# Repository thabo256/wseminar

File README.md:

# W-Seminar

v0.1.0

## Inspiration

[key-ripper by Brian Schwind](https://github.com/bschwind/key-ripper)

## License

This project is licensed under the GNU General Public License (GPL). See the [`LICENSE`](/LICENSE) file in the root for details.

However, the code in the `firmware/` directory is licensed under the MIT License. See the [`LICENSE`](/firmware/LICENSE) file in that directory for details.

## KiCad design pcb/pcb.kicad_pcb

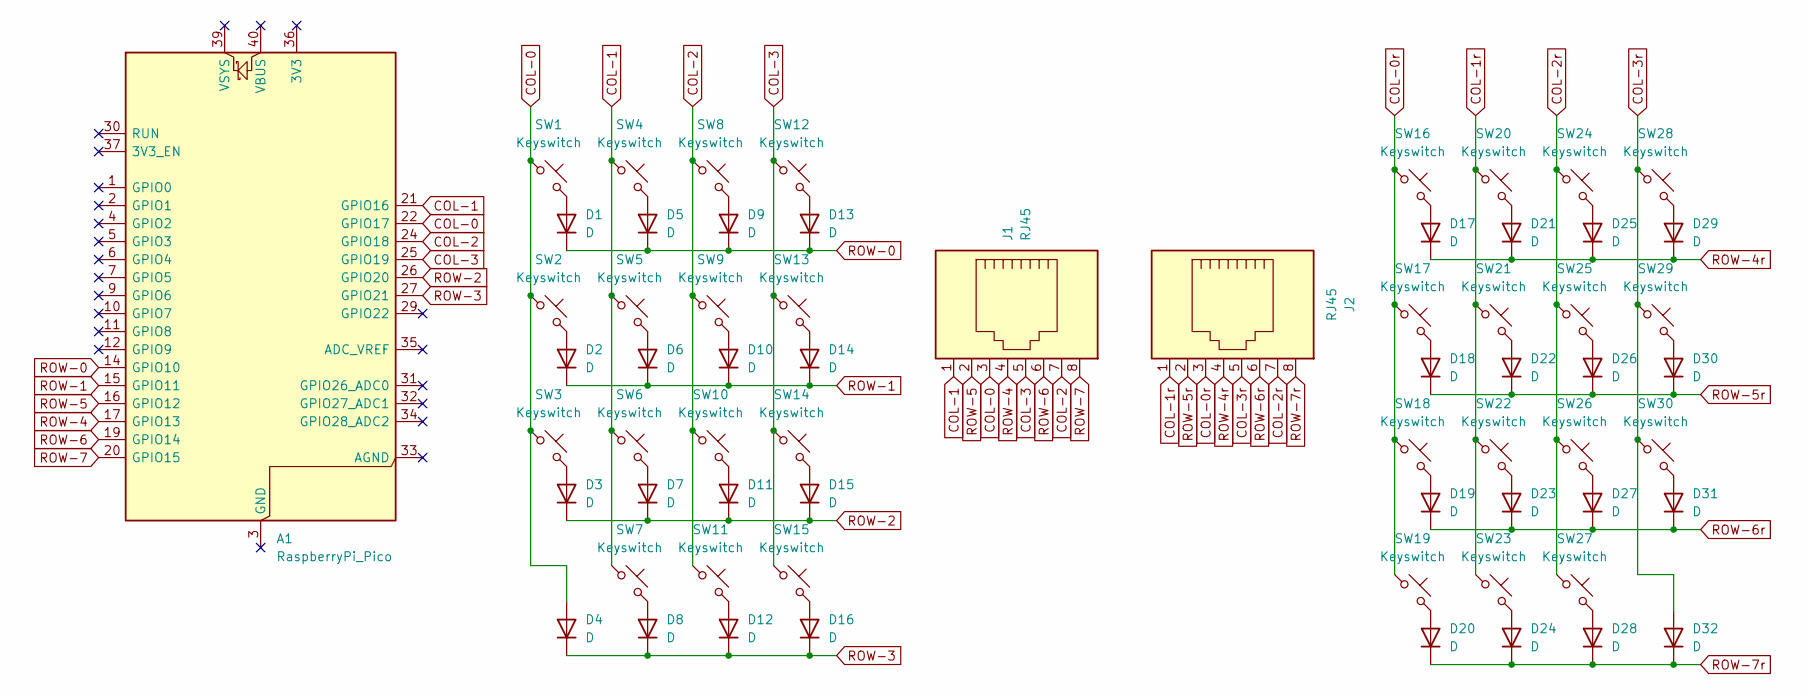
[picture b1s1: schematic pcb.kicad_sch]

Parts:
A1: RaspberryPi_Pico; RaspberryPi_Pico_Common_Unspecified
D1, D2, D3, D4, D5, D6, D7, D8, D9, D10, D11, D12, D13, D14, D15, D16, D17, D18, D19, D20, D21, D22, D23, D24, D25, D26, D27, D28, D29, D30, D31, D32: D; D_DO-35_SOD27_P7.62mm_Horizontal
J1, J2: RJ45; RJ45_Amphenol_54602-x08_Horizontal
SW1, SW2, SW3, SW4, SW5, SW6, SW7, SW8, SW9, SW10, SW11, SW12, SW13, SW14, SW15, SW16, SW17, SW18, SW19, SW20, SW21, SW22, SW23, SW24, SW25, SW26, SW27, SW28, SW29, SW30: Keyswitch; SW_Gateron_LowProfile_HotSwap_THT

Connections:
COL-0: A1.22 (GPIO17), D4.2 (A), J1.3, SW1.1, SW2.1, SW3.1
COL-0r: J2.3, SW16.1, SW17.1, SW18.1, SW19.1
COL-1: A1.21 (GPIO16), J1.1, SW4.1, SW5.1, SW6.1, SW7.1
COL-1r: J2.1, SW20.1, SW21.1, SW22.1, SW23.1
COL-2: A1.24 (GPIO18), J1.7, SW8.1, SW9.1, SW10.1, SW11.1
COL-2r: J2.7, SW24.1, SW25.1, SW26.1, SW27.1
COL-3: A1.25 (GPIO19), J1.5, SW12.1, SW13.1, SW14.1, SW15.1
COL-3r: D32.2 (A), J2.5, SW28.1, SW29.1, SW30.1
unnamed: D1.2 (A), SW1.2
unnamed: D2.2 (A), SW2.2
unnamed: D3.2 (A), SW3.2
unnamed: D5.2 (A), SW4.2
unnamed: D6.2 (A), SW5.2
unnamed: D7.2 (A), SW6.2
unnamed: D8.2 (A), SW7.2
unnamed: D9.2 (A), SW8.2
unnamed: D10.2 (A), SW9.2
unnamed: D11.2 (A), SW10.2
unnamed: D12.2 (A), SW11.2
unnamed: D13.2 (A), SW12.2
unnamed: D14.2 (A), SW13.2
unnamed: D15.2 (A), SW14.2
unnamed: D16.2 (A), SW15.2
unnamed: D17.2 (A), SW16.2
unnamed: D18.2 (A), SW17.2
unnamed: D19.2 (A), SW18.2
unnamed: D20.2 (A), SW19.2
unnamed: D21.2 (A), SW20.2
unnamed: D22.2 (A), SW21.2
unnamed: D23.2 (A), SW22.2
unnamed: D24.2 (A), SW23.2
unnamed: D25.2 (A), SW24.2
unnamed: D26.2 (A), SW25.2
unnamed: D27.2 (A), SW26.2
unnamed: D28.2 (A), SW27.2
unnamed: D29.2 (A), SW28.2
unnamed: D30.2 (A), SW29.2
unnamed: D31.2 (A), SW30.2
ROW-0: A1.14 (GPIO10), D1.1 (K), D5.1 (K), D9.1 (K), D13.1 (K)
ROW-1: A1.15 (GPIO11), D2.1 (K), D6.1 (K), D10.1 (K), D14.1 (K)
ROW-2: A1.26 (GPIO20), D3.1 (K), D7.1 (K), D11.1 (K), D15.1 (K)
ROW-3: A1.27 (GPIO21), D4.1 (K), D8.1 (K), D12.1 (K), D16.1 (K)
ROW-4: A1.17 (GPIO13), J1.4
ROW-4r: D17.1 (K), D21.1 (K), D25.1 (K), D29.1 (K), J2.4
ROW-5: A1.16 (GPIO12), J1.2
ROW-5r: D18.1 (K), D22.1 (K), D26.1 (K), D30.1 (K), J2.2
ROW-6: A1.19 (GPIO14), J1.6
ROW-6r: D19.1 (K), D23.1 (K), D27.1 (K), D31.1 (K), J2.6
ROW-7: A1.20 (GPIO15), J1.8
ROW-7r: D20.1 (K), D24.1 (K), D28.1 (K), D32.1 (K), J2.8

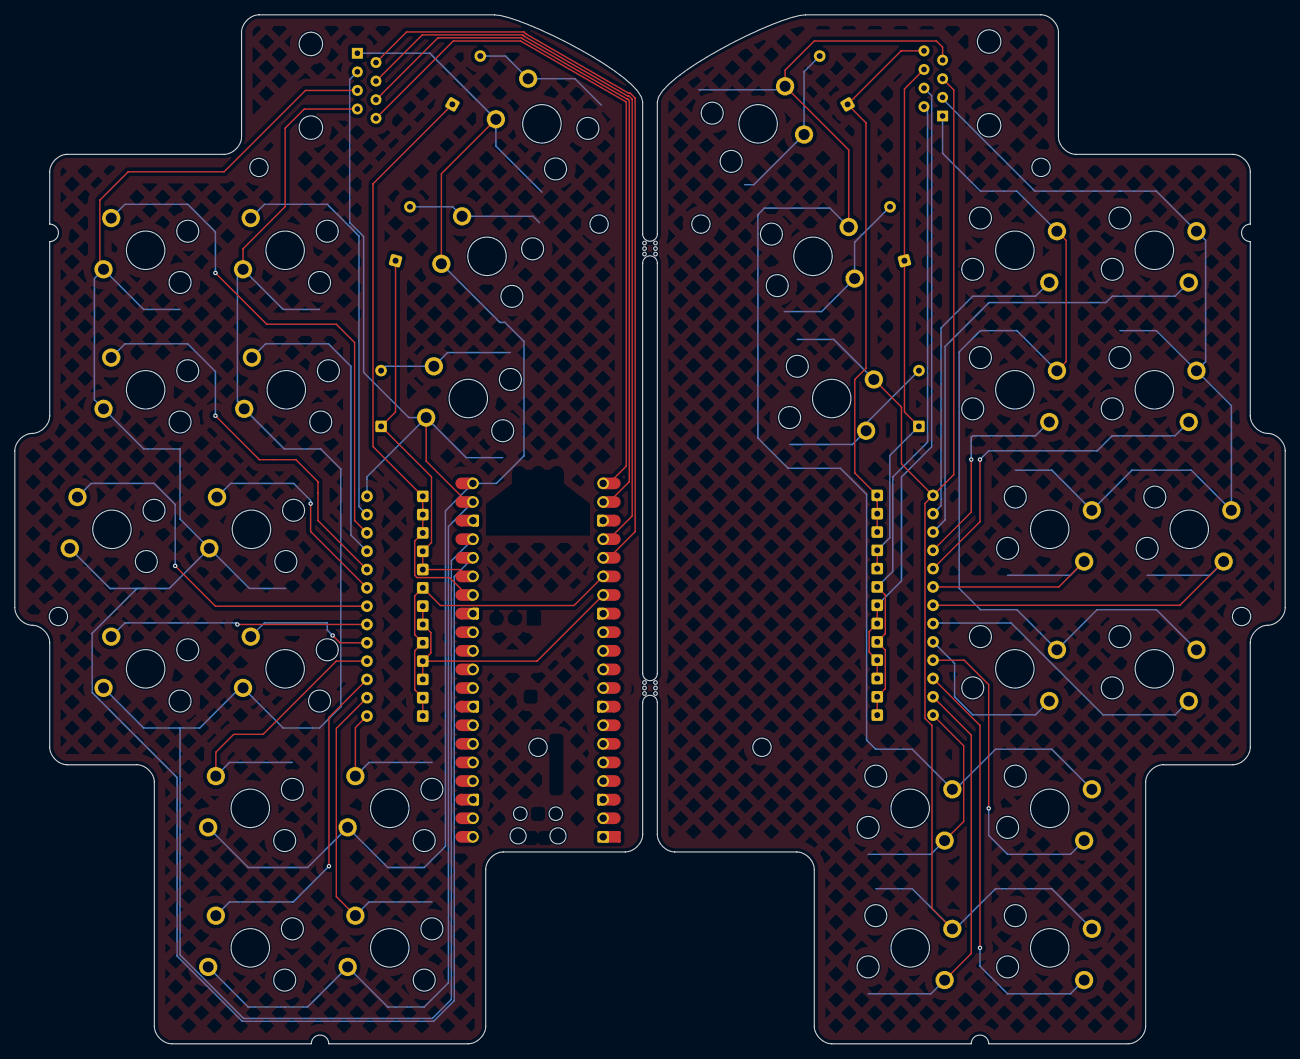
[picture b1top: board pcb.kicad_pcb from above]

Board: 2 copper layers, 173.5 x 140.5 mm, 67 parts (0 on the bottom side), 50 nets.

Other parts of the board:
mouse-bite-2mm-slot, mouse-bite-2mm-slot#2: VAL**; mouse-bite-2mm-slot

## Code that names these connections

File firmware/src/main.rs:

#![no_std]
#![no_main]

use bsp::entry;
use bsp::hal;
use core::{convert::Infallible, panic};
use cortex_m::prelude::*;
use defmt::*;
use defmt_rtt as _;
use embedded_hal::digital::{InputPin, OutputPin, PinState};
use fugit::ExtU32;
use panic_probe as _;
use usb_device::class_prelude::*;
use usb_device::prelude::*;
use usbd_human_interface_device::page::Keyboard;
use usbd_human_interface_device::prelude::*;

// Provide an alias for our BSP so we can switch targets quickly.
use rp_pico as bsp;

use bsp::hal::{
    clocks::{init_clocks_and_plls, Clock},
    pac,
    sio::Sio,
    watchdog::Watchdog,
};

const NUM_COLS: usize = 4;
const NUM_ROWS: usize = 4;

#[entry]
fn main() -> ! {
    info!("Program start");
    let mut pac = pac::Peripherals::take().unwrap();
    let core = pac::CorePeripherals::take().unwrap();
    let mut watchdog = Watchdog::new(pac.WATCHDOG);
    let sio = Sio::new(pac.SIO);

    // External high-speed crystal on the pico board is 12Mhz
    let external_xtal_freq_hz = 12_000_000u32;
    let clocks = init_clocks_and_plls(
        external_xtal_freq_hz,
        pac.XOSC,
        pac.CLOCKS,
        pac.PLL_SYS,
        pac.PLL_USB,
        &mut pac.RESETS,
        &mut watchdog,
    )
    .ok()
    .unwrap();

    let timer = hal::Timer::new(pac.TIMER, &mut pac.RESETS, &clocks);

    let mut delay = cortex_m::delay::Delay::new(core.SYST, clocks.system_clock.freq().to_Hz());

    let pins = bsp::Pins::new(
        pac.IO_BANK0,
        pac.PADS_BANK0,
        sio.gpio_bank0,
        &mut pac.RESETS,
    );

    // Set up keyboard matrix pins.
    let mut rows: [&mut dyn InputPin<Error = Infallible>; NUM_ROWS] = [
        &mut pins.gpio10.into_pull_down_input(),
        &mut pins.gpio11.into_pull_down_input(),
        &mut pins.gpio12.into_pull_down_input(),
        &mut pins.gpio13.into_pull_down_input(),
    ];

    let mut cols: [&mut dyn OutputPin<Error = Infallible>; NUM_COLS] = [
        &mut pins.gpio21.into_push_pull_output(),
        &mut pins.gpio20.into_push_pull_output(),
        &mut pins.gpio19.into_push_pull_output(),
        &mut pins.gpio18.into_push_pull_output(),
    ];

    //USB
    let usb_bus = UsbBusAllocator::new(hal::usb::UsbBus::new(
        pac.USBCTRL_REGS,
        pac.USBCTRL_DPRAM,
        clocks.usb_clock,
        true,
        &mut pac.RESETS,
    ));

    let mut keyboard = UsbHidClassBuilder::new()
        .add_device(
            usbd_human_interface_device::device::keyboard::NKROBootKeyboardConfig::default(),
        )
        .build(&usb_bus);

    let mut usb_dev = UsbDeviceBuilder::new(&usb_bus, UsbVidPid(0x1209, 0x0001))
        .strings(&[StringDescriptors::default()
            .manufacturer("thabo")
            .product("steno keyboard")
            .serial_number("TEST")])
        .unwrap()
        .build();

    let mut led_pin = pins.led.into_push_pull_output();

    let mut input_count_down = timer.count_down();
    input_count_down.start(10.millis());

    let mut tick_count_down = timer.count_down();
    tick_count_down.start(1.millis());

    loop {
        //Poll the keys every 10ms
        if input_count_down.wait().is_ok() {
            let scan = scan(&mut rows, &mut cols, &mut delay);

            let keys = get_keys(&scan);

            match keyboard.device().write_report(keys) {
                Err(UsbHidError::WouldBlock) => {}
                Err(UsbHidError::Duplicate) => {}
                Ok(_) => {}
                Err(e) => {
                    panic!("Failed to write keyboard report: {:?}", e)
                }
            };
        }

        //Tick once per ms
        if tick_count_down.wait().is_ok() {
            match keyboard.tick() {
                Err(UsbHidError::WouldBlock) => {}
                Ok(_) => {}
                Err(e) => {
                    panic!("Failed to process keyboard tick: {:?}", e)
                }
            };
        }

        if usb_dev.poll(&mut [&mut keyboard]) {
            match keyboard.device().read_report() {
                Err(UsbError::WouldBlock) => {
                    //do nothing
                }
                Err(e) => {
                    panic!("Failed to read keyboard report: {:?}", e)
                }
                Ok(leds) => {
                    led_pin.set_state(PinState::from(leds.caps_lock)).ok();
                }
            }
        }
    }
}

fn scan(
    rows: &mut [&mut dyn InputPin<Error = Infallible>; NUM_ROWS],
    columns: &mut [&mut dyn embedded_hal::digital::OutputPin<Error = Infallible>; NUM_COLS],
    delay: &mut cortex_m::delay::Delay,
) -> [[bool; NUM_COLS]; NUM_ROWS] {
    let mut raw_matrix = [[false; NUM_ROWS]; NUM_COLS];

    for (gpio_col, matrix_col) in columns.iter_mut().zip(raw_matrix.iter_mut()) {
        gpio_col.set_high().unwrap();
        delay.delay_us(1);

        for (gpio_row, matrix_row) in rows.iter_mut().zip(matrix_col.iter_mut()) {
            *matrix_row = gpio_row.is_high().unwrap();
        }

        gpio_col.set_low().unwrap();
    }

    raw_matrix
}

const KEY_MAP: [[Keyboard; NUM_COLS]; NUM_ROWS] = [
    [Keyboard::A, Keyboard::B, Keyboard::C, Keyboard::D],
    [Keyboard::E, Keyboard::F, Keyboard::G, Keyboard::H],
    [Keyboard::I, Keyboard::J, Keyboard::K, Keyboard::L],
    [Keyboard::M, Keyboard::N, Keyboard::O, Keyboard::P],
];

fn get_keys(scan: &[[bool; NUM_COLS]; NUM_ROWS]) -> [Keyboard; NUM_COLS * NUM_ROWS] {
    let mut keys = [Keyboard::NoEventIndicated; NUM_COLS * NUM_ROWS];
    let mut index = 0;

    for (row_index, row) in scan.iter().enumerate() {
        for (col_index, &pressed) in row.iter().enumerate() {
            if pressed {
                keys[index] = KEY_MAP[row_index][col_index];
                index += 1;
            }
        }
    }

    keys
}

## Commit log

2025-07-22 add pcb schematic
2025-07-24 add pcb right hand layout
2025-07-26 add pcb left hand layout
2025-07-26 remove unnecessary files
2025-07-27 change pcb diode placement
2025-08-01 add pcb screw holes
2025-08-04 fix pcb holes
2025-08-05 add pcb mouse bites
2025-08-06 remove pcb f.silkscreen drawings
2025-08-07 add pcb filled zone
2025-08-09 add pcb art
